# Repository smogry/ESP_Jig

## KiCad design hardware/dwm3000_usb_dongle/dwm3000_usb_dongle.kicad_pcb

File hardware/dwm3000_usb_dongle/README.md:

# DWM3000 USB Dongle (KiCad 7 project)

STM32C071F8P6 + Qorvo DWM3000 (UWB) USB dongle. Schematic capture is complete
and every part has a footprint assigned; PCB placement is an initial
non-overlapping layout only (routing is not done yet).

> **Rev history**: originally designed around an STM32F042F6P6; swapped to
> STM32C071F8P6 (same TSSOP20 footprint, but a different pinout — see the MCU
> section below for what changed: PF2/NRST is a shared pin instead of a
> dedicated NRST, no separate VDDA pin, and USB_DM/DP are native PA11/PA12
> with no remap needed). A previous revision of this README incorrectly said
> this package "has no NRST pin at all" and left it unconnected -- that was
> wrong (see the corrected MCU section below); pin 6 is wired to J2 nRESET now.

## Files

```
dwm3000_usb_dongle.kicad_pro    KiCad project
dwm3000_usb_dongle.kicad_sch    Schematic (single sheet)
dwm3000_usb_dongle.kicad_pcb    Board with all footprints placed + netlist wired (unrouted)
dwm3000_usb_dongle.net          Generated netlist (for reference / re-import)
dwm3000_usb_dongle_schematic.pdf  Schematic print, for quick review without KiCad
fp-lib-table                    Project footprint-library table (points at dongle.pretty)
dongle.pretty/                  Custom footprints (USB-A receptacle, SWD box header)
previews/                       Rendered PNG/SVG previews of the two custom footprints
extra_symbols/STM32C071F8Px.kicad_sym  Upstream KiCad symbol for the MCU (source of
                                 truth for its pin table; not directly loadable by this
                                 project's KiCad 7.0.11 -- see note in gen_sch.py)
scripts/gen_sch.py               Regenerates the .kicad_sch from scratch
scripts/build_pcb.py             Regenerates the .kicad_pcb from the .net file
```

To regenerate after editing a script: `python3 scripts/gen_sch.py` then re-export
the netlist (`kicad-cli sch export netlist ...`) and re-run `scripts/build_pcb.py`
(requires the `pcbnew` Python module, i.e. a full KiCad install).

## Bill of materials

| Ref | Part | Value | Footprint |
|---|---|---|---|
| U1 | STMicroelectronics STM32C071F8P6 | — | Package_SO:TSSOP-20_4.4x6.5mm_P0.65mm |
| DWM1 | Qorvo DWM3000 module | — | RF_Module:DWM1000 (pin/pitch compatible per datasheet) |
| U2 | Torex XC6220B331MR-G | 3.3V LDO | Package_TO_SOT_SMD:SOT-23-5 (Torex "SOT-25" = JEDEC SOT-23-5) |
| J1 | USB-4AM103AS (Neltron 5075AR-04-XX-XX equivalent) | USB-A receptacle, right-angle THT | dongle:USB_A_Neltron_5075AR-04 (custom) |
| J2 | CnC Tech 3221-10-0300-00 | 1.27mm SMT box header, 2x5 | dongle:BoxHeader_2x05_P1.27mm_CnCTech_3221 (custom) |
| C1, C2 | Ceramic | 10uF | Capacitor_SMD:C_0805_2012Metric |
| C3, C5, C7 | Ceramic | 100nF | Capacitor_SMD:C_0603_1608Metric |
| C6 | Ceramic | 1uF | Capacitor_SMD:C_0603_1608Metric |
| R1, R2 | USB D+/D- series | 22R | Resistor_SMD:R_0603_1608Metric |
| R6 | **DNP** — optional USB D+ pull-up (fitted only if needed, see below) | 1.5k | Resistor_SMD:R_0603_1608Metric |
| R3 | Status LED series | 1k | Resistor_SMD:R_0603_1608Metric |
| R4, R5 | TX/RX LED series | 330R | Resistor_SMD:R_0603_1608Metric |
| R7 | Second status LED series | 1k | Resistor_SMD:R_0603_1608Metric |
| R9 | Power-indicator LED series | 1k | Resistor_SMD:R_0603_1608Metric |
| D1 | Status LED 1 (MCU-driven, PB7/PB8) | LED | LED_SMD:LED_0603_1608Metric |
| D2 | TX activity LED (DWM3000 GPIO3/TXLED) | LED | LED_SMD:LED_0603_1608Metric |
| D3 | RX activity LED (DWM3000 GPIO2/RXLED) | LED | LED_SMD:LED_0603_1608Metric |
| D4 | Status LED 2 (MCU-driven, PB3) | LED | LED_SMD:LED_0603_1608Metric |
| D5 | Power indicator LED (always on, not MCU-driven) | LED | LED_SMD:LED_0603_1608Metric |
| U3 | ST USBLC6-2SC6 | USB D+/D- ESD protection | Package_TO_SOT_SMD:SOT-23-6 |
| F1 | Resettable PTC fuse, VBUS input | 500mA | Fuse:Fuse_0603_1608Metric |
| C4 | Ceramic, VBUS HF bypass (ahead of F1) | 100nF | Capacitor_SMD:C_0603_1608Metric |
| C8 | Ceramic, VBUS HF bypass (LDO input, parallel with C1) | 100nF | Capacitor_SMD:C_0603_1608Metric |

## Power tree

`USB VBUS` -> `J1 pin1` -> `C4 (100nF HF bypass)` -> `F1 (500mA PTC fuse)` ->
`+5V` -> `C1 (10uF) / C8 (100nF)` -> `U2 XC6220B331` -> `+3V3` -> STM32 VDD,
DWM3000 VDD1(AON)/VDD3V3 x2, and D5/R9 (always-on power-indicator LED). U2's
CE is tied directly to VIN (always enabled); it is the "B" series part (CL
auto-discharge, no CE pull-down needed).

`J1 D-/D+` -> `U3 (USBLC6-2SC6 ESD protection)` -> `R1/R2 (22R series)` ->
STM32 PA11/PA12 (USB_DM/USB_DP).

## STM32C071F8P6 pin mapping (TSSOP-20)

Pin table taken from the official KiCad symbol (`MCU_ST_STM32C0:STM32C071F8Px`,
ST-generated data, Oct 2024 — see `extra_symbols/STM32C071F8Px.kicad_sym`).

| Pin | Name | Net | Notes |
|---|---|---|---|
| 1 | PB7/PB8 | LED1_CTRL | sinks D1 (status LED) |
| 2 | PC14 | NC | spare |
| 3 | PC15 | NC | spare |
| 4 | VDD | +3V3 | single supply pin (no separate VDDA on this package) |
| 5 | VSS | GND | |
| 6 | PF2-NRST | NRST | shared pin, defaults to reset input (see below); to J2.10, 100nF to GND (C5) |
| 7 | PA0 | DWM_WAKEUP | drives DWM3000 WAKEUP |
| 8 | PA1 | DWM_RSTN | open-drain reset to DWM3000 RSTn |
| 9 | PA2 | DWM_IRQ | input, DWM3000 IRQ/GPIO8 |
| 10 | PA3 | SPI_CS | GPIO chip-select to DWM3000 SPICSn |
| 11 | PA4 | NC | spare |
| 12 | PA5 | SPI_SCK | SPI1_SCK |
| 13 | PA6 | SPI_MISO | SPI1_MISO |
| 14 | PA7 | SPI_MOSI | SPI1_MOSI |
| 15 | PA8 | NC | spare |
| 16 | PA11 | USB_DM_MCU | native USB_DM (no remap needed, see below) |
| 17 | PA12 | USB_DP_MCU | native USB_DP (no remap needed, see below) |
| 18 | PA13 | SWDIO | |
| 19 | PA14/PA15 | SWCLK | |
| 20 | PB3/PB4/PB5/PB6 | LED2_CTRL | sinks D4 (2nd status LED), using the PB3 identity -- see below |

**No external crystal**: like the F042 this replaced, STM32C071 has HSI48
with a USB-synchronized clock recovery system (CRS), so USB full-speed works
without an external crystal.

**USB pins are native, no remap**: unlike the STM32F042F6P6 this replaced
(which only exposed PA9/PA10 and needed `SYSCFG_CFGR1.PA11_PA12_RMP=1` to use
them as USB), this package brings out true PA11 (USB_DM) and PA12 (USB_DP)
directly on pins 16/17 — firmware just needs to enable the USB peripheral,
no pin remap step required.

**Optional USB D+ pull-up (R6, DNP by default)**: every ST full-speed USB
device peripheral in this IP family (F0/G0/L0/C0) has always had a
software-controlled internal D+ pull-up (`USB_BCDR.DPPU`), so no external
one should be needed here either — but this project's tools couldn't reach
st.com to confirm that against the STM32C071 reference manual directly, so
**R6** (1.5k, USB_DP_MCU to +3V3, right at the R2/PA12 side) is included as
a footprint-only safety net: leave it unpopulated (its default `DNP` state)
and bring the board up first. Only stuff R6 if enumeration fails or the
device isn't detected as full-speed, which would indicate the internal
pull-up either isn't present or isn't enabled by your firmware.

## USB protection, VBUS filtering, power indicator

* **U3 (USBLC6-2SC6)**: dual-line, low-capacitance ESD protection diode
  array (SOT-23-6), inserted in series on D-/D+ between the connector (J1)
  and the existing series resistors (R1/R2) feeding the MCU. Its VBUS pin
  is tied to the (post-fuse) `+5V` rail as the clamp reference, per its
  datasheet. This does not replace R1/R2 — both stay in place downstream
  of U3.
* **F1 (500mA resettable PTC fuse) + C4/C8 (100nF HF bypass)**: VBUS from
  the connector now passes through a small HF bypass cap (C4, right at the
  connector) and a resettable fuse (F1) before becoming the board's `+5V`
  rail; C8 adds a second HF bypass cap at the LDO input, alongside the
  existing bulk cap C1. This protects the host's USB port (and this board)
  from an accidental VBUS short or overcurrent fault downstream, and the
  extra HF caps improve high-frequency supply noise rejection beyond what
  the two 10uF bulk caps (C1/C2) alone provide.
* **D5/R9 (always-on power indicator LED)**: wired straight across `+3V3`
  and `GND` (not MCU-driven, unlike D1/D4), so it lights whenever the LDO
  output is good — independent of firmware/MCU state, useful for confirming
  the board is powered even if the MCU isn't running.

**Pin 6 is a shared PF2/NRST pin, not a dedicated NRST**: unlike the
F042F6P6's pin 4 (a dedicated NRST-only pin), pin 6 on this package is
named **PF2-NRST** in ST's own pin database. This was missed in an earlier
revision of this project: the KiCad symbol used to derive the pin table
(`extra_symbols/STM32C071F8Px.kicad_sym`) only lists this pin's normal
GPIO alternate functions (`PF2`, `RCC_MCO`, `TIM1_CH4`) because the
reset/GPIO duality isn't a regular alternate function — it's controlled by
the **`NRST_MODE[1:0]` option byte**, which isn't part of a KiCad symbol's
pin table at all. Cross-checked against ST's public
[STM32_open_pin_data](https://github.com/STMicroelectronics/STM32_open_pin_data)
MCU database, which does carry the pin's real name (`PF2-NRST`).

Consequences of that, now fixed:
* **Out of the box (factory-default option bytes) this pin behaves as a
  normal NRST reset input**, so it's wired to J2 pin 10 (nRESET) like any
  other STM32 design, with a 100nF filter cap (C5) per the usual
  ST hardware design guidelines (AN2586). Hardware "connect under reset"
  works normally with ST-Link/OpenOCD/PyOCD.
* Firmware *can* reclaim this pin as a plain GPIO (`PF2`) by setting
  `NRST_MODE[1:0]` = GPIO in the option bytes — but this project does not
  do that, and doing so is not recommended without a specific need: ST's
  own community forum documents real pitfalls (the pin still gates
  power-on reset until it sees a valid `VIH(NRST)` level even in GPIO mode,
  and it's possible to end up unable to re-enter reset/debug mode without a
  recovery procedure). Leave `NRST_MODE` at its default and use J2/NRST for
  hardware reset as wired here.

**No separate VDDA pin either**: this package has a single VDD/VSS supply
pair (no analog supply pin to decouple separately), so there's one 100nF
decoupling cap (C3) instead of the F042's two.

**PA14 (SWCLK) is also a shared BOOT0 pin, but it's dormant by default**:
ST's pin database names pin 19 **PA14-BOOT0** — after the PF2-NRST finding
above, this project audited the STM32_open_pin_data XML for every other pin
with a similar hyphenated (option-byte-special) name and found exactly two
more: `PA14-BOOT0` and the OSC pins below. Unlike NRST, this one needed no
hardware fix: **`nBOOT_SEL` defaults to 1 from the factory**, meaning the
physical PA14 pin voltage is *ignored* for boot decisions and boot mode is
taken purely from the `nBOOT0` option bit (default: boot from main flash).
So SWCLK on PA14 works exactly like a normal SWD pin with this design as
wired, with no pull resistor needed. Boot-to-system-bootloader is selected
by setting `nBOOT0`/`nBOOT_SEL` via the SWD debugger (e.g.
STM32CubeProgrammer), not a physical strap — unless someone deliberately
sets `nBOOT_SEL=0` later, which would make PA14's pin voltage matter again
at every reset.

**PC14/PC15 (pins 2/3) are also shared with the LSE oscillator**, named
`PC14-OSCX_IN`/`PC15-OSCX_OUT` — also dormant by default: the LSE oscillator
is off out of reset, and these pins only stop behaving as plain GPIO if
firmware sets the `LSEON` bit in `RCC_CSR`, which this design's firmware has
no reason to do (no RTC crystal is fitted here). Left as spare GPIO (NC) as
before, no hardware change needed.

**Pin 20 is a 4-way multi-bonded pin (PB3/PB4/PB5/PB6 share one physical
pad)**: this is a *different* mechanism from PF2-NRST/PA14-BOOT0 above — it's
not option-byte/reset-time special, just one physical pad wired to four GPIO
peripheral inputs, with a `SYSCFG_CFGR3` register picking which one is
"live" (the other three are forced to passive/digital-input internally).
It's an ordinary peripheral register, not a FLASH option byte: no unlock
sequence, fully rewritable at any time, no bricking risk. **D4 (2nd status
LED) is wired here using the PB3 identity** — firmware must select PB3 in
`SYSCFG_CFGR3` (whatever the factory-default selection turns out to be)
before configuring the pin as a GPIO output, or D4 won't respond.

## DWM3000 pin mapping (24-pin castellated module)

| Pin | Name | Net |
|---|---|---|
| 1 | EXTON | NC (device-enable output, unused) |
| 2 | WAKEUP | DWM_WAKEUP |
| 3 | RSTn | DWM_RSTN |
| 4 | GPIO7 | NC |
| 5 | VDD1 (AON) | +3V3 |
| 6, 7 | VDD3V3 | +3V3 |
| 8, 16, 21, 23, 24 | VSS | GND |
| 9–11, 14, 15 | GPIO6/5/4, GPIO1, GPIO0 | NC (spare) |
| 12 | GPIO3/TXLED | TXLED_CTRL -> D2 |
| 13 | GPIO2/RXLED | RXLED_CTRL -> D3 |
| 17 | SPICSn | SPI_CS |
| 18 | SPIMOSI | SPI_MOSI |
| 19 | SPIMISO | SPI_MISO |
| 20 | SPICLK | SPI_SCK |
| 22 | IRQ/GPIO8 | DWM_IRQ |

## SWD connector J2 (standard ARM 10-pin Cortex-Debug pinout)

| Pin | Signal | Net |
|---|---|---|
| 1 | VTref | +3V3 |
| 2 | SWDIO | SWDIO |
| 3, 5, 9 | GND | GND |
| 4 | SWCLK | SWCLK |
| 6 | SWO | NC (Cortex-M0+ has no trace/SWO) |
| 7 | KEY | NC |
| 8 | TDI | NC (SWD only, no JTAG on Cortex-M0+) |
| 10 | nRESET | NRST (STM32 PF2-NRST, pin 6 — see MCU section above) |

## Custom footprints

* **USB_A_Neltron_5075AR-04** — right-angle THT USB-A receptacle. Pad
  geometry (4x ⌀0.92 signal pins at 2.5/2.0mm pitch spanning 7.0mm, 2x ⌀2.3
  mounting pins spanning 13.14mm) matches the dimensions given in the
  connector's own datasheet (Neltron 5075AR-04-XX-XX).
* **BoxHeader_2x05_P1.27mm_CnCTech_3221** — 1.27mm-pitch SMT box header, 2x5,
  gull-wing pads, row spacing 2.76mm per the CnC Tech 3221-10-0300-00
  datasheet. Pin numbering follows the standard ARM SWD odd/even convention
  (pins 1,3,5,7,9 one row; 2,4,6,8,10 the other).

## Validation performed

* `kicad-cli sch export netlist` parses the schematic cleanly and produces
  the expected 21 signal nets (including `/NRST`, `/LED2_CTRL`,
  `/USB_DM_RAW`, `/USB_DP_RAW`, `/VBUS_RAW`) + `+3V3`/`+5V`/`GND`, with
  every remaining "spare"/unused pin explicitly flagged no-connect (verified
  pin-by-pin against the intended design above).
* All 28 components (27 fitted + DNP R6) loaded their real KiCad footprints
  (including the 2 custom ones) and were placed non-overlapping on a board
  with all 44 nets wired from the netlist (`dwm3000_usb_dongle.kicad_pcb`).
  R6 is marked excluded from BOM/position files to match its schematic DNP flag.
* Schematic and PCB were rendered to PDF/SVG/PNG for visual review.
* U3 (USBLC6-2SC6)'s pin table was taken verbatim from its parent symbol
  (`USBLC6-2P6` in the system `Power_Protection.kicad_sym`, extends-flattened
  the same way as DWM3000/DWM1000). Its 4 signal pins are only 2.54mm apart,
  so they're routed out with a short vertical jog (`jog_label()` in
  `gen_sch.py`) rather than straight stubs, to keep the net labels legible.

### A note on the STM32C071F8Px symbol

This project's KiCad install (7.0.11, the current Ubuntu package) ships a
`MCU_ST_STM32C0` library that only goes up to STM32C011/STM32C031 —
STM32C071 was added to the official KiCad libraries later, in a newer
generator format (KiCad 9/10-style, e.g. `show_name`/`do_not_autoplace`
sub-fields) that this KiCad 7.0.11 cannot parse. `extra_symbols/STM32C071F8Px.kicad_sym`
is the real upstream symbol (fetched from the current kicad-symbols `master`
on GitLab) kept here as the authoritative source for the pin table; `scripts/gen_sch.py`
reproduces the same pins in the older, KiCad-7-compatible symbol syntax
(`build_stm32c071_symbol()`) rather than embedding that file directly. If/when
this project is opened in a newer KiCad, the vendored symbol can be dropped in
as-is.

## Not done yet (next steps for whoever picks this up)

* Final PCB placement (the current layout is just a tidy grid, grouped by
  subsystem) and routing.
* DRC / 3D check inside the KiCad GUI.
* Antenna keep-out area on the DWM3000 side per its datasheet §6.1 (no
  ground copper/components under or beside the module's ceramic antenna).
* USB D+/D- trace length matching + controlled impedance if desired.

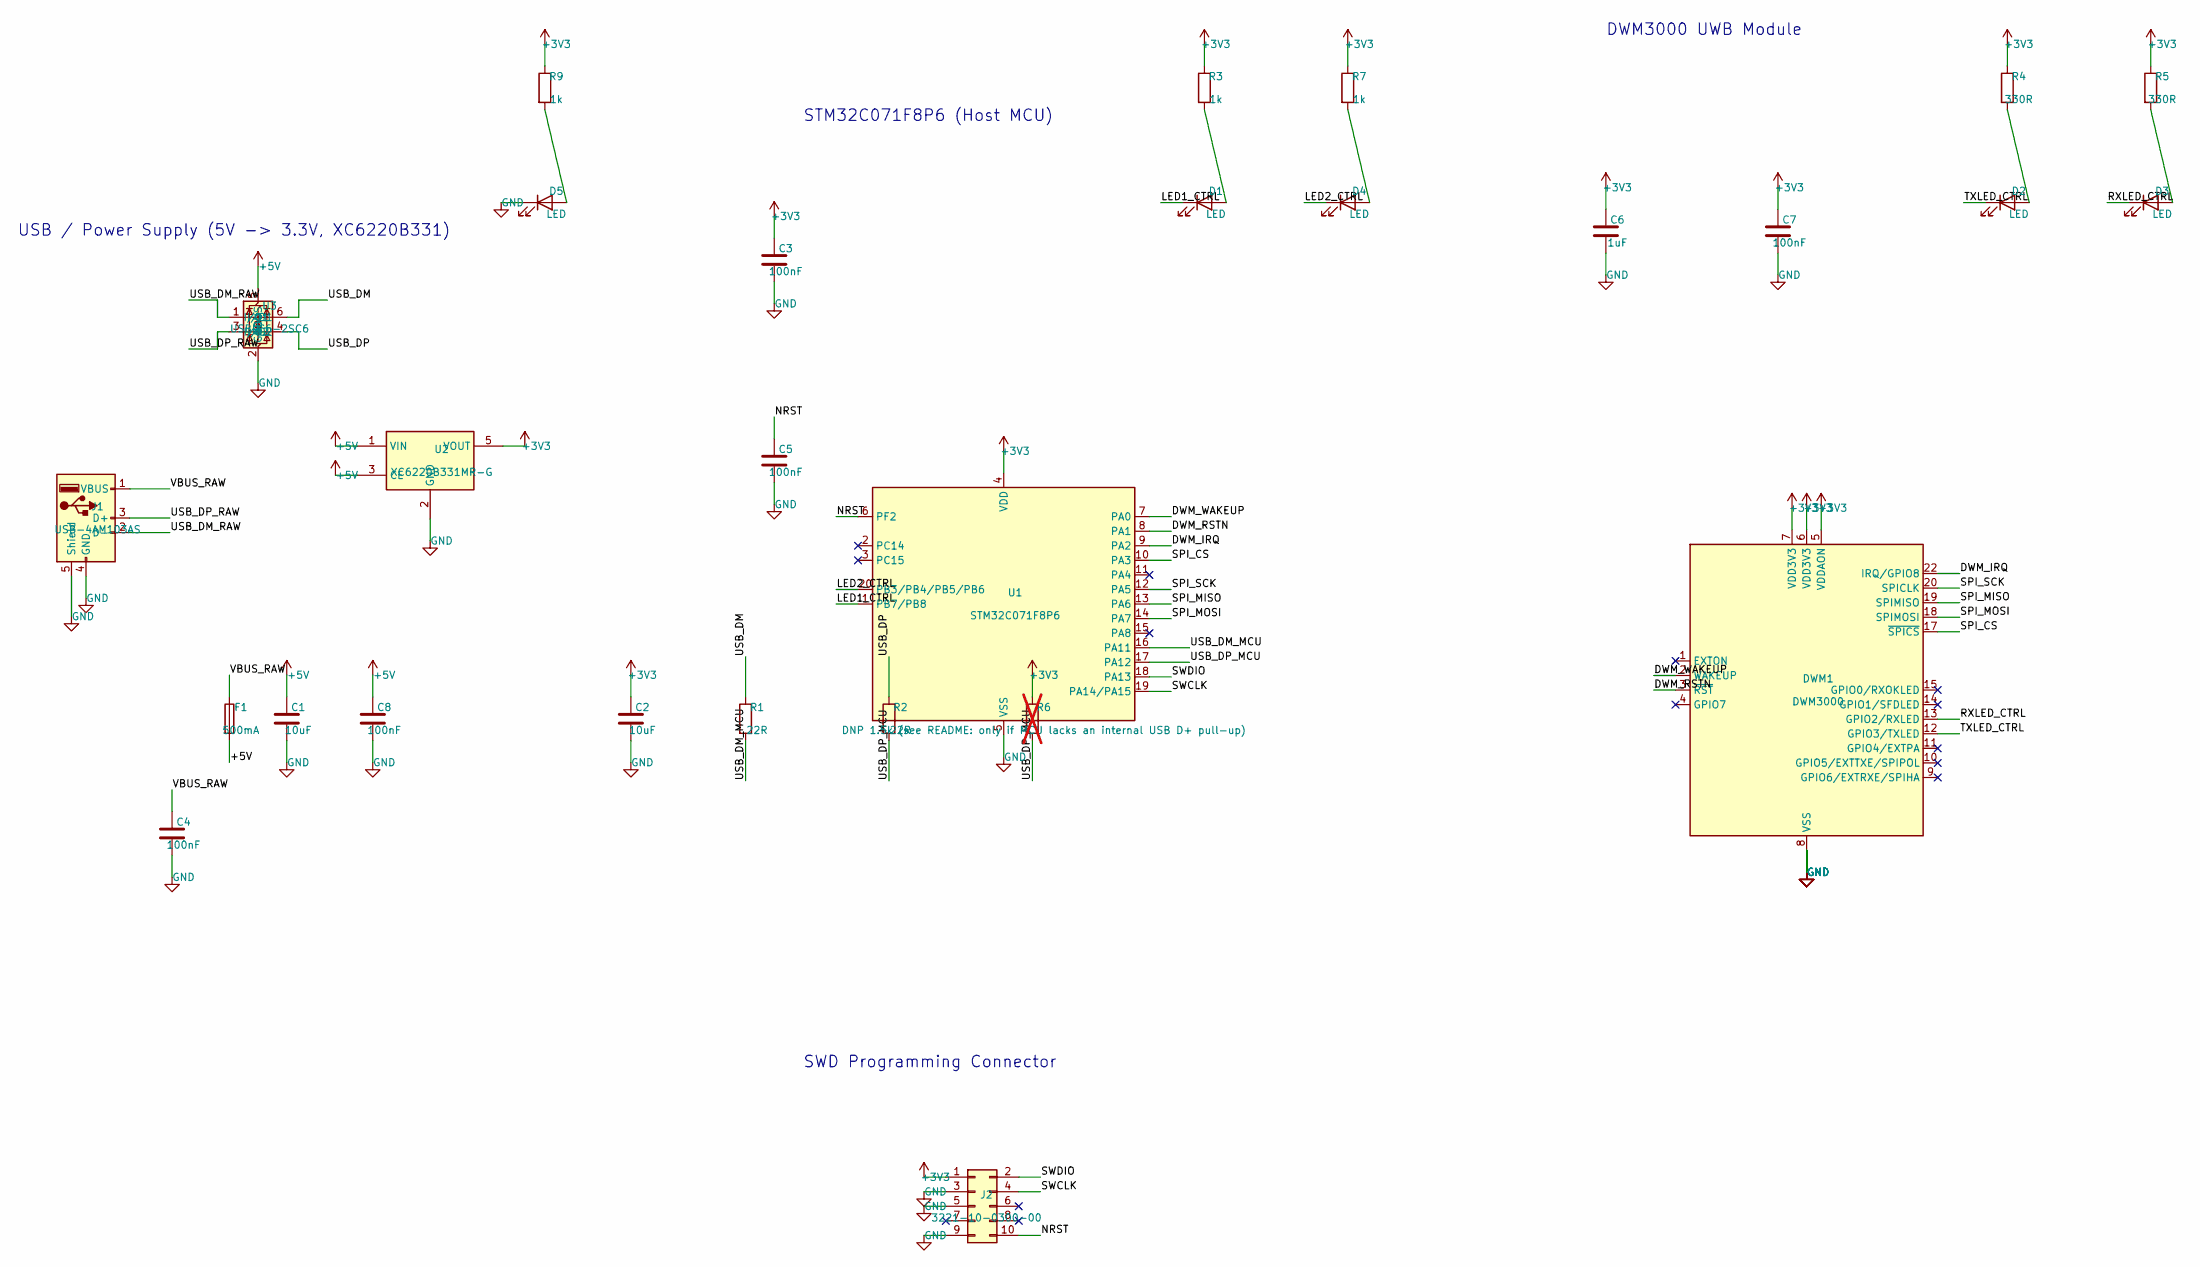
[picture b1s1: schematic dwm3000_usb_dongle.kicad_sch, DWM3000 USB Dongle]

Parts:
C1, C2: 10uF; C_0805_2012Metric
C3, C4, C5, C7, C8: 100nF; C_0603_1608Metric
C6: 1uF; C_0603_1608Metric
D1, D2, D3, D4, D5: LED; LED_0603_1608Metric
DWM1: DWM3000; DWM1000
F1: 500mA; Fuse_0603_1608Metric
J1: USB-4AM103AS; USB_A_Neltron_5075AR-04
J2: 3221-10-0300-00; BoxHeader_2x05_P1.27mm_CnCTech_3221
R1, R2: 22R; R_0603_1608Metric
R3, R7, R9: 1k; R_0603_1608Metric
R4, R5: 330R; R_0603_1608Metric
R6: DNP 1.5k (see README: only if MCU lacks an intern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; R_0603_1608Metric; not fitted
U1: STM32C071F8P6; TSSOP-20_4.4x6.5mm_P0.65mm
U2: XC6220B331MR-G; SOT-23-5
U3: USBLC6-2SC6; SOT-23-6

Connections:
+3V3: C2.1, C3.1, C6.1, C7.1, DWM1.5 (VDDAON), DWM1.6 (VDD3V3), DWM1.7 (VDD3V3), J2.1, R3.1, R4.1, R5.1, R6.1, R7.1, R9.1, U1.4 (VDD), U2.5 (VOUT)
+5V: C1.1, C8.1, F1.2, U2.1 (VIN), U2.3 (CE), U3.5 (VBUS)
/DWM_IRQ: DWM1.22 (IRQ/GPIO8), U1.9 (PA2)
/DWM_RSTN: DWM1.3 (~RST), U1.8 (PA1)
/DWM_WAKEUP: DWM1.2 (WAKEUP), U1.7 (PA0)
/LED1_CTRL: D1.1 (K), U1.1 (PB7/PB8)
/LED2_CTRL: D4.1 (K), U1.20 (PB3/PB4/PB5/PB6)
/NRST: C5.1, J2.10, U1.6 (PF2)
/RXLED_CTRL: D3.1 (K), DWM1.13 (GPIO2/RXLED)
/SPI_CS: DWM1.17 (~SPICS), U1.10 (PA3)
/SPI_MISO: DWM1.19 (SPIMISO), U1.13 (PA6)
/SPI_MOSI: DWM1.18 (SPIMOSI), U1.14 (PA7)
/SPI_SCK: DWM1.20 (SPICLK), U1.12 (PA5)
/SWCLK: J2.4, U1.19 (PA14/PA15)
/SWDIO: J2.2, U1.18 (PA13)
/TXLED_CTRL: D2.1 (K), DWM1.12 (GPIO3/TXLED)
/USB_DM: R1.1, U3.6 (I/O1)
/USB_DM_MCU: R1.2, U1.16 (PA11)
/USB_DM_RAW: J1.2 (D-), U3.1 (I/O1)
/USB_DP: R2.1, U3.4 (I/O2)
/USB_DP_MCU: R2.2, R6.2, U1.17 (PA12)
/USB_DP_RAW: J1.3 (D+), U3.3 (I/O2)
/VBUS_RAW: C4.1, F1.1, J1.1 (VBUS)
GND: C1.2, C2.2, C3.2, C4.2, C5.2, C6.2, C7.2, C8.2, D5.1 (K), DWM1.8 (VSS), DWM1.16 (VSS), DWM1.21 (VSS), DWM1.23 (VSS), DWM1.24 (VSS), J1.4 (GND), J1.5 (Shield), J2.3, J2.5, J2.9, U1.5 (VSS), U2.2 (GND), U3.2 (GND)
unnamed: D1.2 (A), R3.2
unnamed: D2.2 (A), R4.2
unnamed: D3.2 (A), R5.2
unnamed: D4.2 (A), R7.2
unnamed: D5.2 (A), R9.2

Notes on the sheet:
USB / Power Supply (5V -> 3.3V, XC6220B331)
STM32C071F8P6 (Host MCU)
SWD Programming Connector
DWM3000 UWB Module

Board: 2 copper layers, 28 parts (0 on the bottom side), 29 nets, no tracks yet.

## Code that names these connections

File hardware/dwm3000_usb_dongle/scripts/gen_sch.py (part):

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# (single VDD/VSS supply pair) -- both differ from the STM32F042F6Px this
# replaced. See extra_symbols/STM32C071F8Px.kicad_sym for the source symbol.
STM32_PINS = {
    "1":  (-25.4, 0,      0,   2.54, "PB7/PB8"),
    "2":  (-25.4, 10.16,  0,   2.54, "PC14"),
    "3":  (-25.4, 7.62,   0,   2.54, "PC15"),
    "4":  (0,     22.86,  270, 2.54, "VDD"),
    "5":  (0,     -22.86, 90,  2.54, "VSS"),
    "6":  (-25.4, 15.24,  0,   2.54, "PF2"),
    "7":  (25.4,  15.24,  180, 2.54, "PA0"),
    "8":  (25.4,  12.7,   180, 2.54, "PA1"),
    "9":  (25.4,  10.16,  180, 2.54, "PA2"),
    "10": (25.4,  7.62,   180, 2.54, "PA3"),
    "11": (25.4,  5.08,   180, 2.54, "PA4"),
    "12": (25.4,  2.54,   180, 2.54, "PA5"),
    "13": (25.4,  0,      180, 2.54, "PA6"),
    "14": (25.4,  -2.54,  180, 2.54, "PA7"),
    "15": (25.4,  -5.08,  180, 2.54, "PA8"),
    "16": (25.4,  -7.62,  180, 2.54, "PA11"),
    "17": (25.4,  -10.16, 180, 2.54, "PA12"),
    "18": (25.4,  -12.7,  180, 2.54, "PA13"),
    "19": (25.4,  -15.24, 180, 2.54, "PA14/PA15"),
    "20": (-25.4, 2.54,   0,   2.54, "PB3/PB4/PB5/PB6"),
}

DWM_PINS = {
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
# ---- Power rails ----
# USB connector: VBUS -> F1 (resettable fuse) -> +5V; D-/D+ -> U3 (ESD array) -> R1/R2
label_pin(J1, "1", "VBUS_RAW", stub_len=7.0)        # to F1
label_pin(J1, "2", "USB_DM_RAW", stub_len=7.0)      # to U3 (ESD protection)
label_pin(J1, "3", "USB_DP_RAW", stub_len=7.0)      # to U3 (ESD protection)
wire_to_power(J1, "4", "GND")
wire_to_power(J1, "5", "GND", stub_len=7.0)

# F1: resettable fuse, VBUS_RAW (from connector) -> +5V (protected rail)
label_pin(F1, "1", "VBUS_RAW")
label_pin(F1, "2", "+5V")

# C4: HF bypass right at the connector, ahead of the fuse
label_pin(C4, "1", "VBUS_RAW"); wire_to_power(C4, "2", "GND")

# U3 (USBLC6-2SC6): dual-line USB ESD protection, inserted in series between
# the raw connector D-/D+ and the series resistors R1/R2 feeding the MCU.
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# only 2.54mm apart, so each pin is routed out with a short vertical jog
# (up for the pin1/6 pair, down for pin3/4) to keep the four net labels
# from overlapping each other/the symbol's own pin numbers.
jog_label(U3, "1", "USB_DM_RAW", -2.0, -3.0, -5.0)
jog_label(U3, "6", "USB_DM", 2.0, -3.0, 5.0)         # feeds R1 (unchanged downstream net name)
jog_label(U3, "3", "USB_DP_RAW", -2.0, 3.0, -5.0)
jog_label(U3, "4", "USB_DP", 2.0, 3.0, 5.0)         # feeds R2 (unchanged downstream net name)
wire_to_power(U3, "2", "GND")
wire_to_power(U3, "5", "+5V")

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wire_to_power(D5, "1", "GND")    # D5 cathode(K) -> GND

# ---- USB series resistors R1 (D-) / R2 (D+) between connector and MCU ----
label_pin(R1, "1", "USB_DM", stub_len=7.0, label_angle=90)
label_pin(R1, "2", "USB_DM_MCU", stub_len=7.0, label_angle=90)
label_pin(R2, "1", "USB_DP", stub_len=7.0, label_angle=90)
label_pin(R2, "2", "USB_DP_MCU", stub_len=7.0, label_angle=90)

# R6: DNP (do-not-populate) external USB D+ pull-up, only stuffed if bring-up
# testing shows the STM32C071's internal D+ pull-up isn't present/sufficient.
wire_to_power(R6, "1", "+3V3")
label_pin(R6, "2", "USB_DP_MCU", stub_len=7.0, label_angle=90)

# ---- STM32 U1 (STM32C071F8Px: PF2/NRST shared pin, no separate VDDA pin) ----
nc_pin(U1, "2")     # PC14 spare
nc_pin(U1, "3")     # PC15 spare
nc_pin(U1, "11")    # PA4 spare
nc_pin(U1, "15")    # PA8 spare
label_pin(U1, "20", "LED2_CTRL")    # PB3 (of the PB3/PB4/PB5/PB6 multi-bond pad; see README)

label_pin(U1, "1", "LED1_CTRL")                     # PB7/PB8 -> LED1 cathode
wire_to_power(U1, "4", "+3V3")                      # VDD
wire_to_power(U1, "5", "GND")                       # VSS
label_pin(U1, "6", "NRST")                          # PF2-NRST (reset by default; NRST_MODE option byte can turn it into plain PF2)
label_pin(U1, "7", "DWM_WAKEUP")                    # PA0
label_pin(U1, "8", "DWM_RSTN")                      # PA1
label_pin(U1, "9", "DWM_IRQ")                       # PA2
label_pin(U1, "10", "SPI_CS")                       # PA3
label_pin(U1, "12", "SPI_SCK")                      # PA5
label_pin(U1, "13", "SPI_MISO")                     # PA6
label_pin(U1, "14", "SPI_MOSI")                     # PA7
label_pin(U1, "16", "USB_DM_MCU", stub_len=7.0)      # PA11 (native USB_DM, no remap needed)
label_pin(U1, "17", "USB_DP_MCU", stub_len=7.0)      # PA12 (native USB_DP, no remap needed)
label_pin(U1, "18", "SWDIO")                        # PA13
label_pin(U1, "19", "SWCLK")                        # PA14/PA15

# C3: single VDD/VSS decoupling cap (this package has no separate VDDA pin)
wire_to_power(C3, "1", "+3V3"); wire_to_power(C3, "2", "GND")
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label_pin(C5, "1", "NRST")
wire_to_power(C5, "2", "GND")

# LED1 status indicator: +3V3 -R3- LED1(A->K) - LED1_CTRL(U1 PB8 sinks)
wire_to_power(R3, "1", "+3V3")
wire_between(R3, "2", D1, "2")   # R3.2 -> LED1 anode(A, pin2)
label_pin(D1, "1", "LED1_CTRL")  # LED1 cathode(K) -> PB8 net

# LED2 (second MCU-driven indicator): +3V3 -R7- LED4(A->K) - LED2_CTRL(U1 PB3 sinks)
wire_to_power(R7, "1", "+3V3")
wire_between(R7, "2", D4, "2")   # R7.2 -> LED4 anode(A, pin2)
label_pin(D4, "1", "LED2_CTRL")  # LED4 cathode(K) -> PB3 net

# ---- SWD connector J2 (ARM 10-pin standard) ----
wire_to_power(J2, "1", "+3V3")   # VTref
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nc_pin(J2, "7")                  # KEY
nc_pin(J2, "8")                  # TDI - not present on Cortex-M0+ (SWD only)
wire_to_power(J2, "9", "GND")
label_pin(J2, "10", "NRST")      # nRESET -> STM32 PF2-NRST (pin 6)

# ---- DWM3000 module ----
nc_pin(DWM1, "1")   # EXTON (device-enable output; not used)
label_pin(DWM1, "2", "DWM_WAKEUP")
label_pin(DWM1, "3", "DWM_RSTN")
nc_pin(DWM1, "4")   # GPIO7 spare
wire_to_power(DWM1, "5", "+3V3")   # VDDAON
wire_to_power(DWM1, "6", "+3V3")   # VDD3V3
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nc_pin(DWM1, "9")   # GPIO6 spare
nc_pin(DWM1, "10")  # GPIO5 spare
nc_pin(DWM1, "11")  # GPIO4 spare
label_pin(DWM1, "12", "TXLED_CTRL")  # GPIO3/TXLED
label_pin(DWM1, "13", "RXLED_CTRL")  # GPIO2/RXLED
nc_pin(DWM1, "14")  # GPIO1 spare
nc_pin(DWM1, "15")  # GPIO0 spare
wire_to_power(DWM1, "16", "GND")
label_pin(DWM1, "17", "SPI_CS")
label_pin(DWM1, "18", "SPI_MOSI")
label_pin(DWM1, "19", "SPI_MISO")
label_pin(DWM1, "20", "SPI_SCK")
wire_to_power(DWM1, "21", "GND")
label_pin(DWM1, "22", "DWM_IRQ")
wire_to_power(DWM1, "23", "GND")
wire_to_power(DWM1, "24", "GND")

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# TX/RX activity LEDs driven directly by DWM3000 GPIO pins
wire_to_power(R4, "1", "+3V3")
sch.wire(R4.pin_end("2"), D2.pin_end("2"))
label_pin(D2, "1", "TXLED_CTRL")

wire_to_power(R5, "1", "+3V3")
sch.wire(R5.pin_end("2"), D3.pin_end("2"))
label_pin(D3, "1", "RXLED_CTRL")

# ---- Section titles ----
sch.text("USB / Power Supply (5V -> 3.3V, XC6220B331)", (18, 50), size=2.0)
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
